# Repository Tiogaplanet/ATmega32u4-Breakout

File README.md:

# ATmega32u4 Breakout
 A breakout board for the ATmega32u4, designed using KiCad.

# Features
 The ATmega32u4 comes in a 44-pin quad-flat no-leads (QFN) package or a thin quad flat pack (TQFP). This breakout board adapts the TQFP to make prototyping and integration with larger projects easy.  Every pin of the ATmega32u4 is pulled out to a breadboard-friendly size of 57.15mm x 18.86mm with 2.54mm pin spacing.  The result is an ATmega32u4 in a more conventional dual-inline package (DIP).  Solder pads for a 16MHz crystal and a pair of 22pF capacitors are included.

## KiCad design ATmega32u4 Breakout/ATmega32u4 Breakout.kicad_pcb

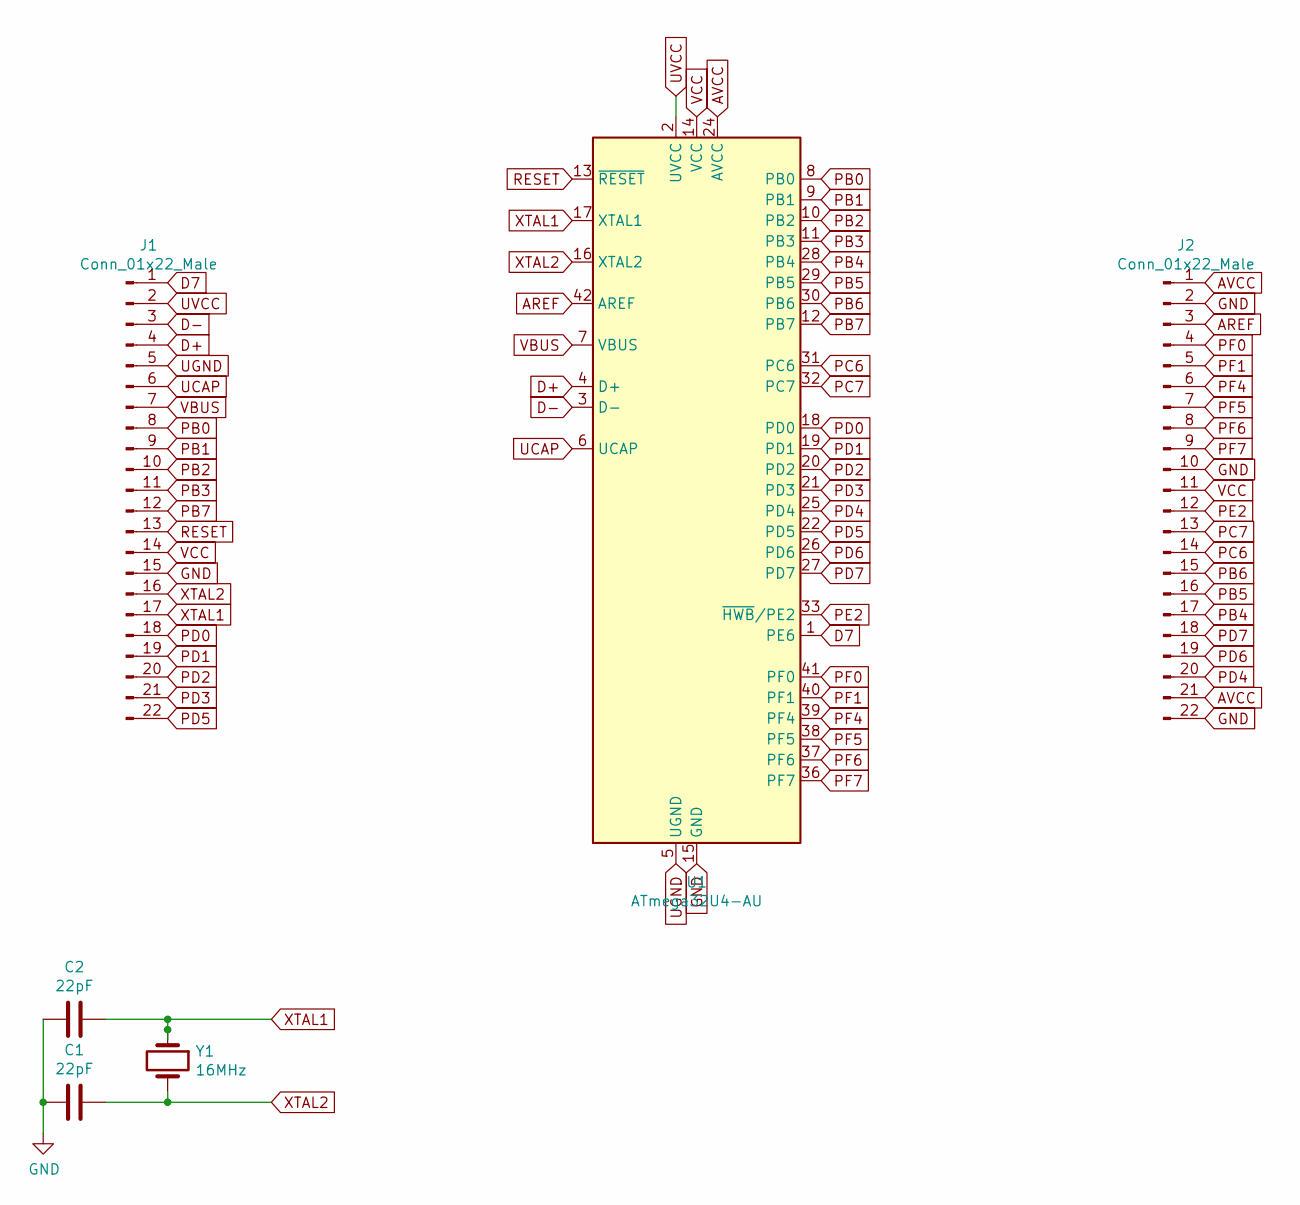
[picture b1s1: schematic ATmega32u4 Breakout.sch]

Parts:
C1, C2: 22pF; C_Disc_D3.0mm_W1.6mm_P2.50mm
J1, J2: Conn_01x22_Male; PinHeader_1x22_P2.54mm_Vertical
U1: ATmega32U4-AU; TQFP-44_10x10mm_P0.8mm
Y1: 16MHz; Crystal_HC49-U_Vertical

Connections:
AREF: J2.3, U1.42 (AREF)
AVCC: J2.1, J2.21, U1.24 (AVCC), U1.44 (AVCC)
D7: J1.1, U1.1 (PE6)
D+: J1.4, U1.4 (D+)
D-: J1.3, U1.3 (D-)
GND: C1.2, C2.2, J1.15, J2.2, J2.10, J2.22, U1.15 (GND), U1.23 (GND), U1.35 (GND), U1.43 (GND)
PB0: J1.8, U1.8 (PB0)
PB1: J1.9, U1.9 (PB1)
PB2: J1.10, U1.10 (PB2)
PB3: J1.11, U1.11 (PB3)
PB4: J2.17, U1.28 (PB4)
PB5: J2.16, U1.29 (PB5)
PB6: J2.15, U1.30 (PB6)
PB7: J1.12, U1.12 (PB7)
PC6: J2.14, U1.31 (PC6)
PC7: J2.13, U1.32 (PC7)
PD0: J1.18, U1.18 (PD0)
PD1: J1.19, U1.19 (PD1)
PD2: J1.20, U1.20 (PD2)
PD3: J1.21, U1.21 (PD3)
PD4: J2.20, U1.25 (PD4)
PD5: J1.22, U1.22 (PD5)
PD6: J2.19, U1.26 (PD6)
PD7: J2.18, U1.27 (PD7)
PE2: J2.12, U1.33 (~HWB~/PE2)
PF0: J2.4, U1.41 (PF0)
PF1: J2.5, U1.40 (PF1)
PF4: J2.6, U1.39 (PF4)
PF5: J2.7, U1.38 (PF5)
PF6: J2.8, U1.37 (PF6)
PF7: J2.9, U1.36 (PF7)
RESET: J1.13, U1.13 (~RESET)
UCAP: J1.6, U1.6 (UCAP)
UGND: J1.5, U1.5 (UGND)
UVCC: J1.2, U1.2 (UVCC)
VBUS: J1.7, U1.7 (VBUS)
VCC: J1.14, J2.11, U1.14 (VCC), U1.34 (VCC)
XTAL1: C2.1, J1.17, U1.17 (XTAL1), Y1.1
XTAL2: C1.1, J1.16, U1.16 (XTAL2), Y1.2

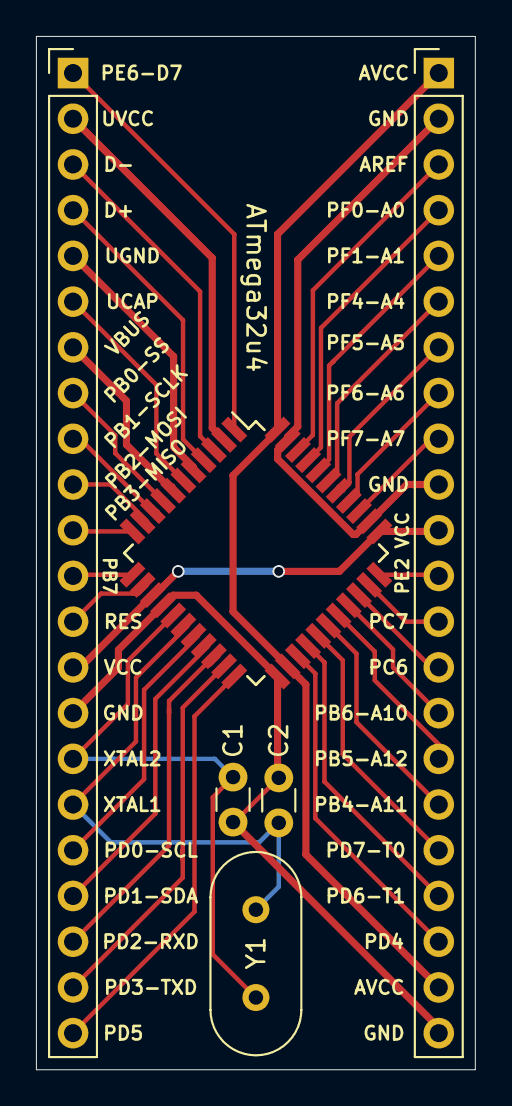
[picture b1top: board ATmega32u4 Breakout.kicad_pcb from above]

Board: 2 copper layers, 24.4 x 57.4 mm, 6 parts (0 on the bottom side), 39 nets.

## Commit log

2020-11-05 Somthing is wrong with last push
    Initial commit didn't make it to github.com.
2020-11-05 Update README.md
    Added feature section.
2020-11-06 Added some pin labels.
2020-11-06 Moving labels around
2020-11-08 Lots of work over the weekend.
    Nearly done, gerber files made too. I think it's ready to be turned into PCB.
